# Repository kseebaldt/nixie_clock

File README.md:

# nixie_clock
ESP32 based nixie clock

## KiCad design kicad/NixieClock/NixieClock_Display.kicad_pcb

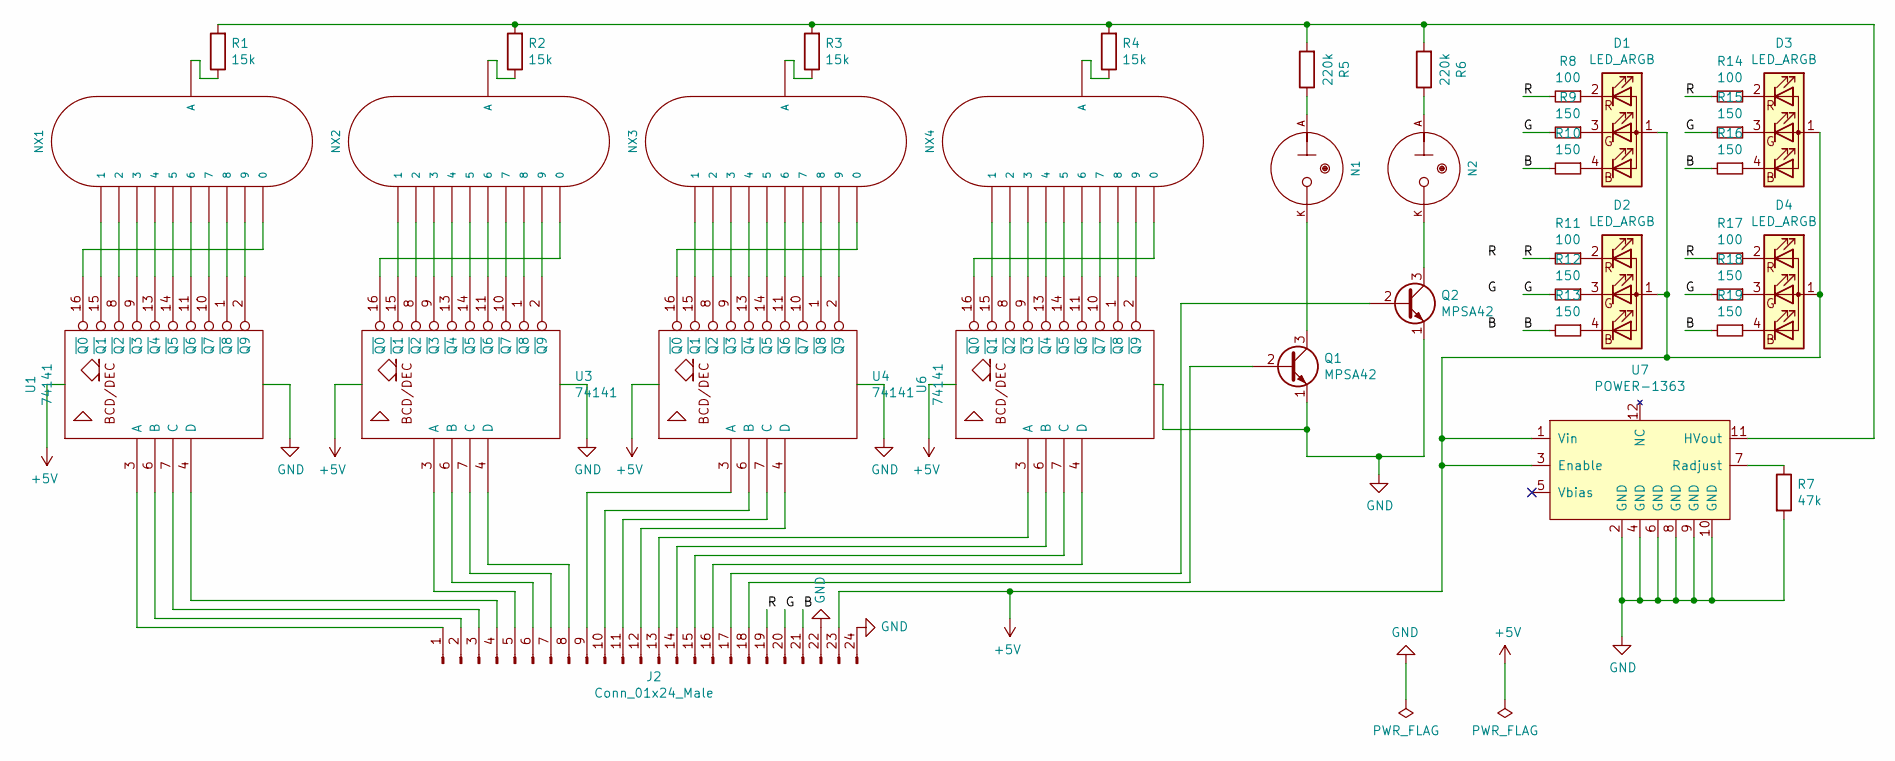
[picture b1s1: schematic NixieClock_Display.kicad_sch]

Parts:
D1, D2, D3, D4: LED_ARGB; LED_RGB_1210
J2: Conn_01x24_Male; PinHeader_1x24_P2.54mm_Vertical
N1, N2: INS-1
NX1, NX2, NX3, NX4: IN-12A; nixies-us-IN-12-DSUB
Q1, Q2: MPSA42; TO-92_Inline
R1, R2, R3, R4: 15k; R_Axial_DIN0204_L3.6mm_D1.6mm_P7.62mm_Horizontal
R5, R6: 220k; R_Axial_DIN0204_L3.6mm_D1.6mm_P7.62mm_Horizontal
R7: 47k; R_Axial_DIN0204_L3.6mm_D1.6mm_P7.62mm_Horizontal
R8, R11, R14, R17: 100; R_0805_2012Metric
R9, R10, R12, R13, R15, R16, R18, R19: 150; R_0805_2012Metric
U1, U3, U4, U6: 74141; DIP-16_W7.62mm_Socket
U7: POWER-1363; PinHeader_2x06_P2.54mm_Vertical

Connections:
+5V: D1.1 (A), D2.1 (A), D3.1 (A), D4.1 (A), J2.23, U1.5 (VCC), U3.5 (VCC), U4.5 (VCC), U6.5 (VCC), U7.1 (Vin), U7.3 (Enable)
/B: J2.21, R10.2, R13.2, R16.2, R19.2
/G: J2.20, R9.2, R12.2, R15.2, R18.2
/R: J2.19, R8.2, R11.2, R14.2, R17.2
GND: J2.22, J2.24, Q1.1 (E), Q2.1 (E), R7.2, U1.12 (GND), U3.12 (GND), U4.12 (GND), U6.12 (GND), U7.2 (GND), U7.4 (GND), U7.6 (GND), U7.8 (GND), U7.9 (GND), U7.10 (GND)
unnamed: D1.2 (RK), R8.1
unnamed: D1.3 (GK), R9.1
unnamed: D1.4 (BK), R10.1
unnamed: D2.2 (RK), R11.1
unnamed: D2.3 (GK), R12.1
unnamed: D2.4 (BK), R13.1
unnamed: D3.2 (RK), R14.1
unnamed: D3.3 (GK), R15.1
unnamed: D3.4 (BK), R16.1
unnamed: D4.2 (RK), R17.1
unnamed: D4.3 (GK), R18.1
unnamed: D4.4 (BK), R19.1
unnamed: J2.1, U1.3 (A)
unnamed: J2.2, U1.6 (B)
unnamed: J2.3, U1.7 (C)
unnamed: J2.4, U1.4 (D)
unnamed: J2.5, U3.3 (A)
unnamed: J2.6, U3.6 (B)
unnamed: J2.7, U3.7 (C)
unnamed: J2.8, U3.4 (D)
unnamed: J2.9, U4.3 (A)
unnamed: J2.10, U4.6 (B)
unnamed: J2.11, U4.7 (C)
unnamed: J2.12, U4.4 (D)
unnamed: J2.13, U6.3 (A)
unnamed: J2.14, U6.6 (B)
unnamed: J2.15, U6.7 (C)
unnamed: J2.16, U6.4 (D)
unnamed: J2.17, Q2.2 (B)
unnamed: J2.18, Q1.2 (B)
unnamed: N1.A, R5.1
unnamed: N1.K, Q1.3 (C)
unnamed: N2.A, R6.1
unnamed: N2.K, Q2.3 (C)
unnamed: NX1.0, U1.16 (~Q0)
unnamed: NX1.1, U1.15 (~Q1)
unnamed: NX1.2, U1.8 (~Q2)
unnamed: NX1.3, U1.9 (~Q3)
unnamed: NX1.4, U1.13 (~Q4)
unnamed: NX1.5, U1.14 (~Q5)
unnamed: NX1.6, U1.11 (~Q6)
unnamed: NX1.7, U1.10 (~Q7)
unnamed: NX1.8, U1.1 (~Q8)
unnamed: NX1.9, U1.2 (~Q9)
unnamed: NX1.A, R1.1
unnamed: NX2.0, U3.16 (~Q0)
unnamed: NX2.1, U3.15 (~Q1)
unnamed: NX2.2, U3.8 (~Q2)
unnamed: NX2.3, U3.9 (~Q3)
unnamed: NX2.4, U3.13 (~Q4)
unnamed: NX2.5, U3.14 (~Q5)
unnamed: NX2.6, U3.11 (~Q6)
unnamed: NX2.7, U3.10 (~Q7)
unnamed: NX2.8, U3.1 (~Q8)
unnamed: NX2.9, U3.2 (~Q9)
unnamed: NX2.A, R2.1
unnamed: NX3.0, U4.16 (~Q0)
unnamed: NX3.1, U4.15 (~Q1)
unnamed: NX3.2, U4.8 (~Q2)
unnamed: NX3.3, U4.9 (~Q3)
unnamed: NX3.4, U4.13 (~Q4)
unnamed: NX3.5, U4.14 (~Q5)
unnamed: NX3.6, U4.11 (~Q6)
unnamed: NX3.7, U4.10 (~Q7)
unnamed: NX3.8, U4.1 (~Q8)
unnamed: NX3.9, U4.2 (~Q9)
unnamed: NX3.A, R3.1
unnamed: NX4.0, U6.16 (~Q0)
unnamed: NX4.1, U6.15 (~Q1)
unnamed: NX4.2, U6.8 (~Q2)
unnamed: NX4.3, U6.9 (~Q3)
unnamed: NX4.4, U6.13 (~Q4)
unnamed: NX4.5, U6.14 (~Q5)
unnamed: NX4.6, U6.11 (~Q6)
unnamed: NX4.7, U6.10 (~Q7)
unnamed: NX4.8, U6.1 (~Q8)
unnamed: NX4.9, U6.2 (~Q9)
unnamed: NX4.A, R4.1
unnamed: R1.2, R2.2, R3.2, R4.2, R5.2, R6.2, U7.11 (HVout)
unnamed: R7.1, U7.7 (Radjust)

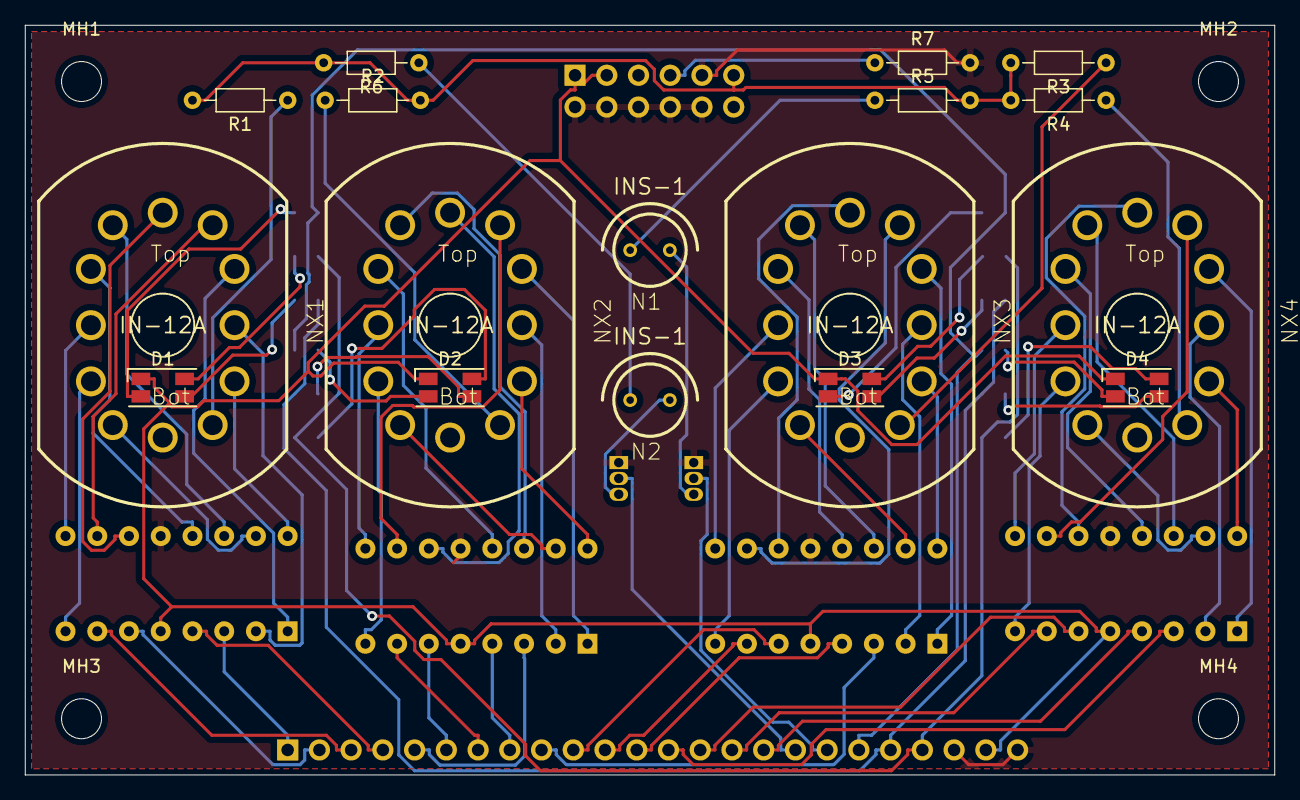
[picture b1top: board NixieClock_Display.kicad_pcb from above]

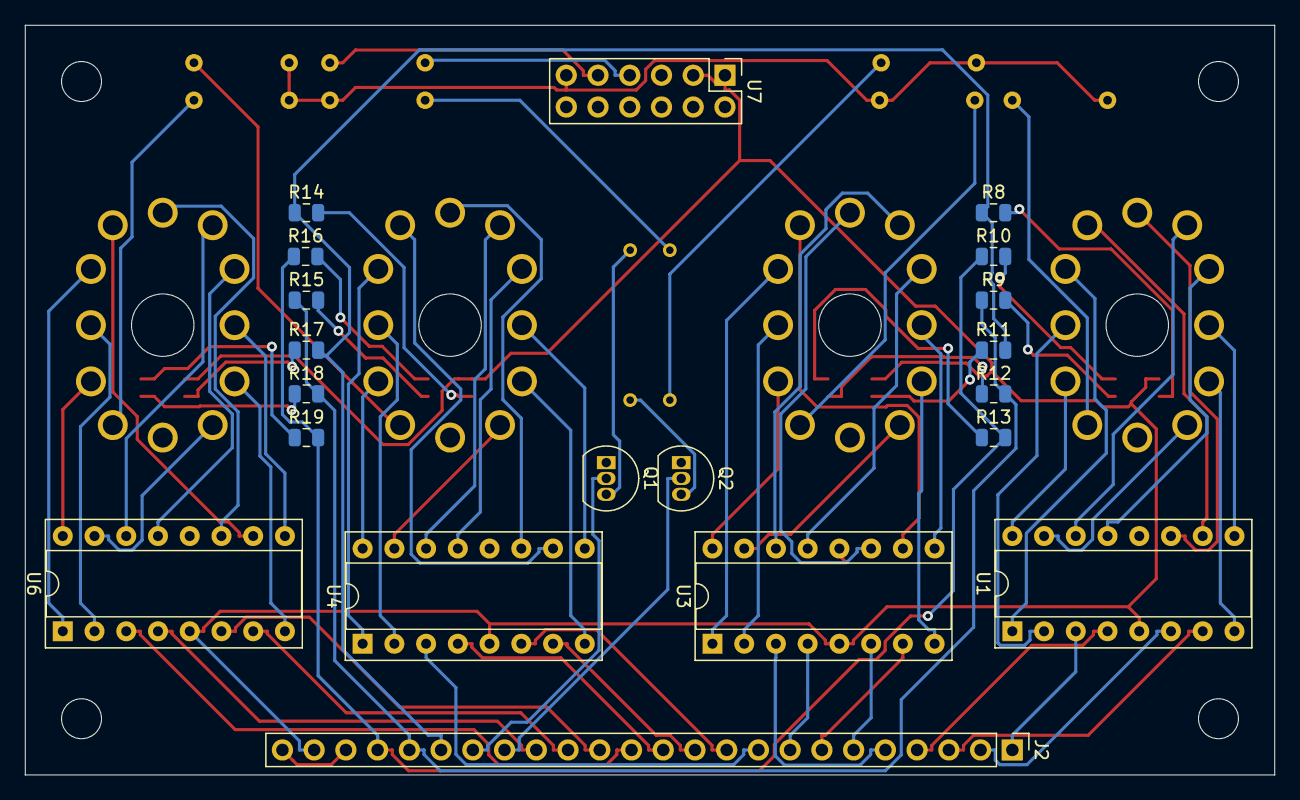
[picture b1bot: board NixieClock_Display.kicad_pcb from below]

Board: 2 copper layers, 100.0 x 60.0 mm, 41 parts (20 on the bottom side), 85 nets.

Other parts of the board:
MH1, MH2, MH3, MH4: MountingHole_3.2mm_M3

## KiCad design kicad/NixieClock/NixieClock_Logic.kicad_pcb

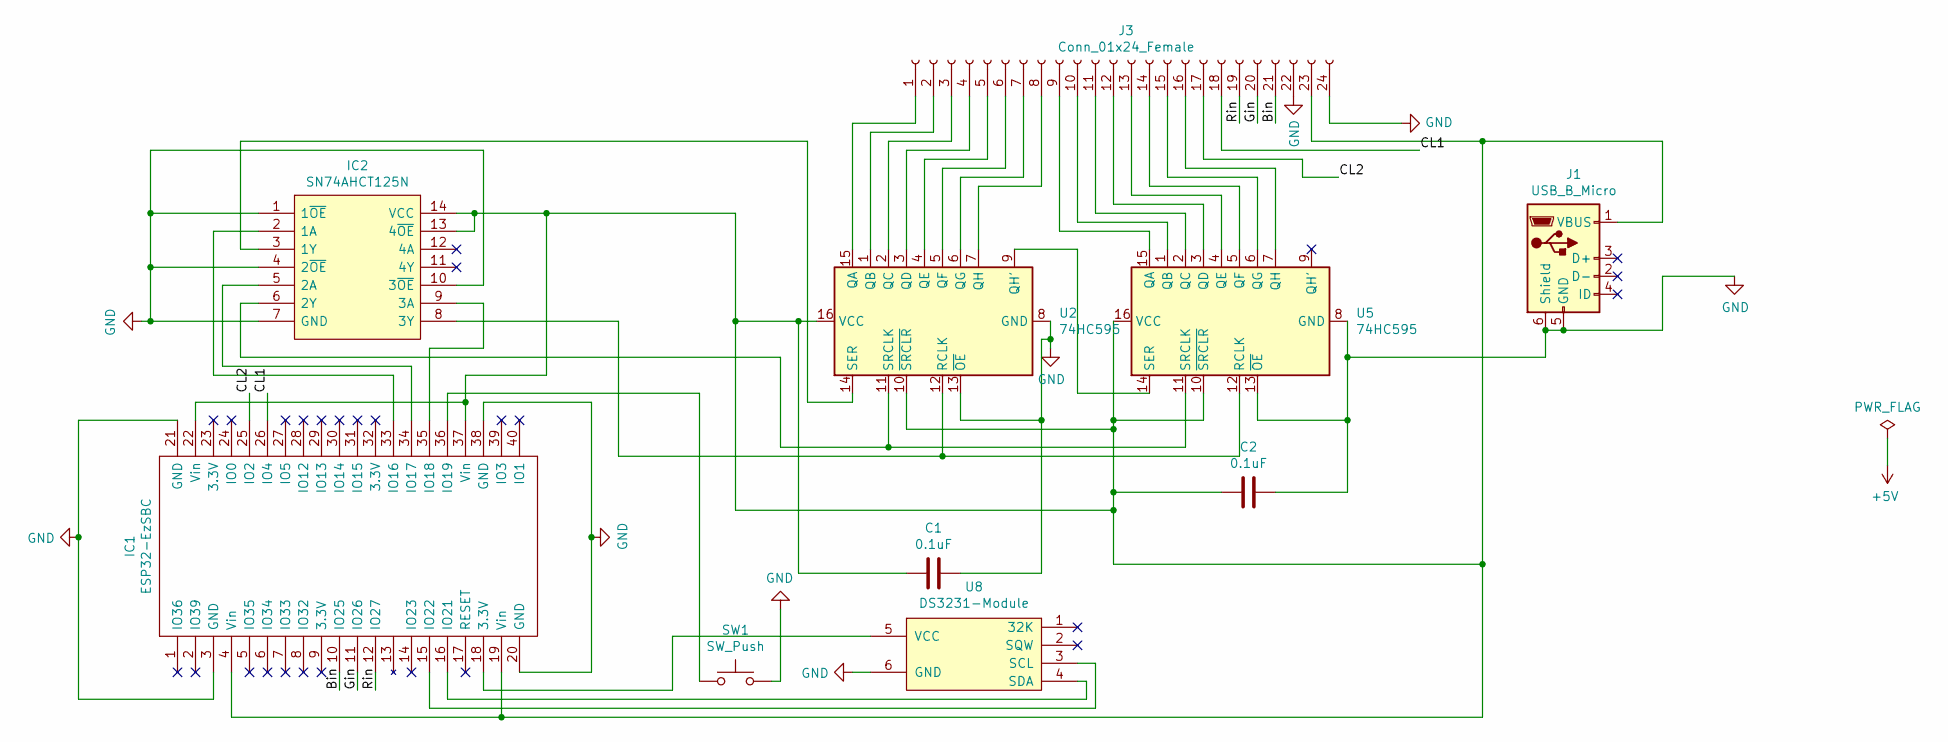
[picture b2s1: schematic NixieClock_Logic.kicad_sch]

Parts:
C1, C2: 0.1uF; C_Disc_D7.5mm_W5.0mm_P5.00mm
IC1: ESP32-EzSBC
IC2: SN74AHCT125N; DIP-14_W7.62mm_Socket
J1: USB_B_Micro; USB_Micro-B_Molex-105017-0001
J3: Conn_01x24_Female; PinHeader_1x24_P2.54mm_Vertical
SW1: SW_Push; PinHeader_1x02_P2.54mm_Vertical
U2, U5: 74HC595; DIP-16_W7.62mm_Socket
U8: DS3231-Module; PinSocket_1x06_P2.54mm_Vertical

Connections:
/Bin: IC1.10 (IO25), J3.21
/CL1: IC1.26 (IO4), J3.18
/CL2: IC1.25 (IO2), J3.17
/Gin: IC1.11 (IO26), J3.20
/Rin: IC1.12 (IO27), J3.19
GND: C1.2, C2.2, IC1.3 (GND), IC1.20 (GND), IC1.21 (GND), IC1.38 (GND), IC2.1 (1~OE), IC2.4 (2~OE), IC2.7 (GND), IC2.10 (3~OE), J1.5 (GND), J1.6 (Shield), J3.22, J3.24, SW1.2, U2.8 (GND), U2.13 (~OE), U5.8 (GND), U5.13 (~OE), U8.6 (GND)
unnamed: C1.1, C2.1, IC1.4 (Vin), IC1.19 (Vin), IC1.22 (Vin), IC1.37 (Vin), IC2.13 (4~OE), IC2.14 (VCC), J1.1 (VBUS), J3.23, U2.10 (~SRCLR), U2.16 (VCC), U5.10 (~SRCLR), U5.16 (VCC)
unnamed: IC1.15 (IO22), U8.3 (SCL)
unnamed: IC1.16 (IO21), U8.4 (SDA)
unnamed: IC1.18 (3.3V), U8.5 (VCC)
unnamed: IC1.33 (IO16), IC2.2 (1A)
unnamed: IC1.34 (IO17), IC2.5 (2A)
unnamed: IC1.35 (IO18), IC2.9 (3A)
unnamed: IC1.36 (IO19), SW1.1
unnamed: IC2.3 (1Y), U2.14 (SER)
unnamed: IC2.6 (2Y), U2.11 (SRCLK), U5.11 (SRCLK)
unnamed: IC2.8 (3Y), U2.12 (RCLK), U5.12 (RCLK)
unnamed: J3.1, U2.15 (QA)
unnamed: J3.2, U2.1 (QB)
unnamed: J3.3, U2.2 (QC)
unnamed: J3.4, U2.3 (QD)
unnamed: J3.5, U2.4 (QE)
unnamed: J3.6, U2.5 (QF)
unnamed: J3.7, U2.6 (QG)
unnamed: J3.8, U2.7 (QH)
unnamed: J3.9, U5.15 (QA)
unnamed: J3.10, U5.1 (QB)
unnamed: J3.11, U5.2 (QC)
unnamed: J3.12, U5.3 (QD)
unnamed: J3.13, U5.4 (QE)
unnamed: J3.14, U5.5 (QF)
unnamed: J3.15, U5.6 (QG)
unnamed: J3.16, U5.7 (QH)
unnamed: U2.9 (QH'), U5.14 (SER)

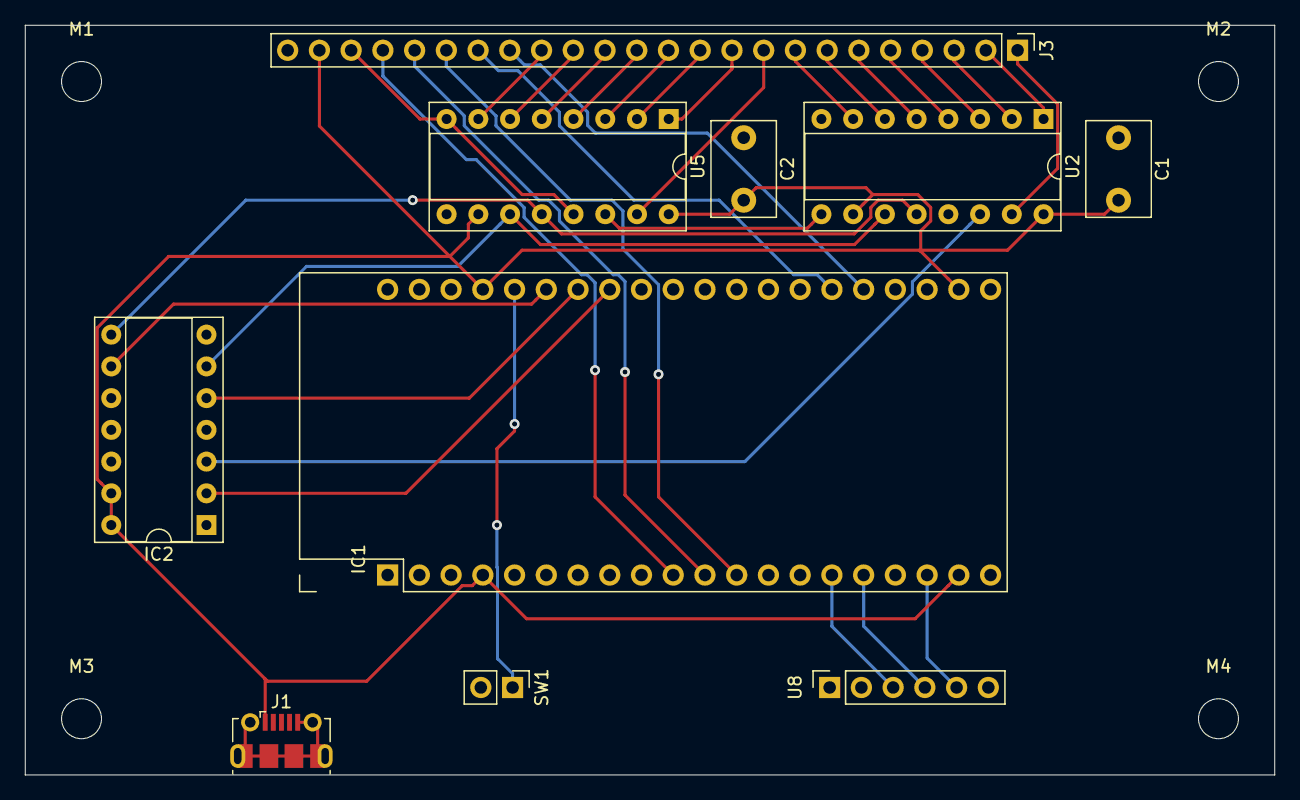
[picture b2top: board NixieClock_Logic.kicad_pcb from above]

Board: 2 copper layers, 100.0 x 60.0 mm, 14 parts (0 on the bottom side), 34 nets.

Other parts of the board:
M1, M2, M3, M4: MountingHole_3.2mm_M3

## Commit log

2019-06-18 empty project
2019-06-18 add pin mappings
2019-06-18 show current time
2019-07-06 test leds and nixies
2019-07-08 Add display driver library
2019-07-08 basic clock functionality
2019-07-08 fix date & year
2019-07-09 add BLE and config
2019-07-10 add config change callbacks
2019-07-10 add LedDriver class
2019-07-10 config change callback for time zone
2019-07-11 use catch unit test framework; finish led driver
2019-07-15 add button library
2019-07-15 add display mode button
2019-07-15 add OTA support
2019-07-17 button is pull down instead of pull up
2019-09-14 switch button to use internal pullup
2019-09-14 add DS3231 rtc to restore time on startup
2019-12-14 add 12/24 hour mode
2021-02-05 Add kicad files
2022-10-14 Migrate tests to unity
2022-10-14 Update wifi event constant
2022-10-14 Add github action for build
2022-10-14 Run native unit tests in CI
2022-10-14 Add ArduinoFake library to native target
2022-10-14 Remove fake arduino header
2022-10-14 Upgrade kicad files to v6
2022-10-14 Add device specific unit test
2024-05-14 Add wokwi simulator files
2024-05-14 Resave kicad files in latest version
